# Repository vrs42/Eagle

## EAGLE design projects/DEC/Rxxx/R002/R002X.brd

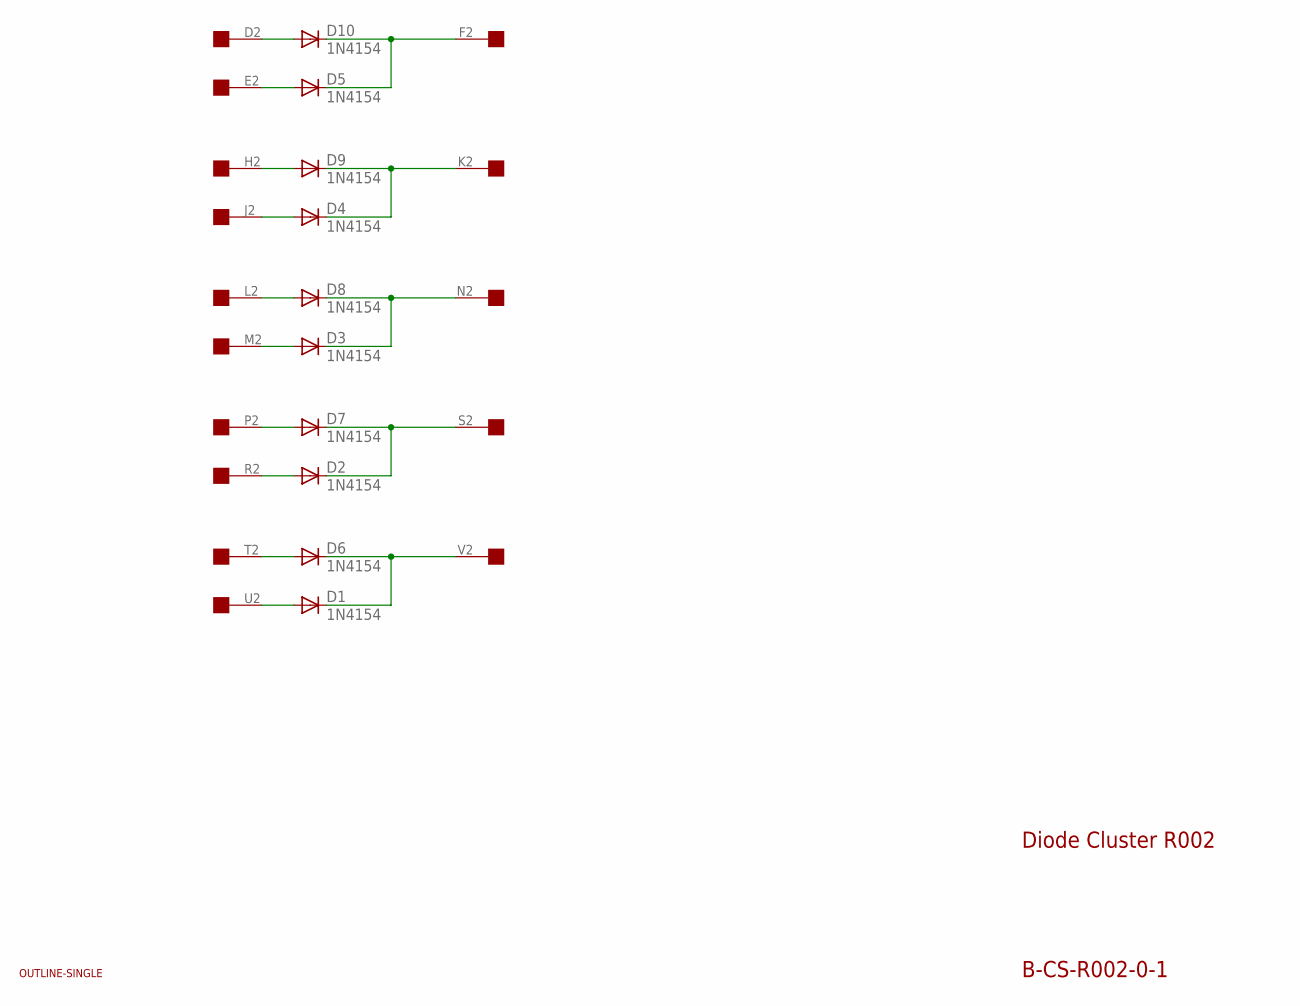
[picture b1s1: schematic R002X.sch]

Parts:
D1, D2, D3, D4, D5, D6, D7, D8, D9, D10: 1N4154; DO35-10
U$1: OUTLINE-SINGLE; SINGLE
U$2: EDGE-1; EDGE-CON1

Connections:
unnamed: D10.A, U$2.D2
unnamed: D5.A, U$2.E2
unnamed: D5.C, D10.C, U$2.F2
unnamed: D9.A, U$2.H2
unnamed: D4.A, U$2.J2
unnamed: D4.C, D9.C, U$2.K2
unnamed: D8.A, U$2.L2
unnamed: D3.A, U$2.M2
unnamed: D3.C, D8.C, U$2.N2
unnamed: D7.A, U$2.P2
unnamed: D2.A, U$2.R2
unnamed: D2.C, D7.C, U$2.S2
unnamed: D6.A, U$2.T2
unnamed: D1.A, U$2.U2
unnamed: D1.C, D6.C, U$2.V2

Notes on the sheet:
Diode Cluster R002
B-CS-R002-0-1

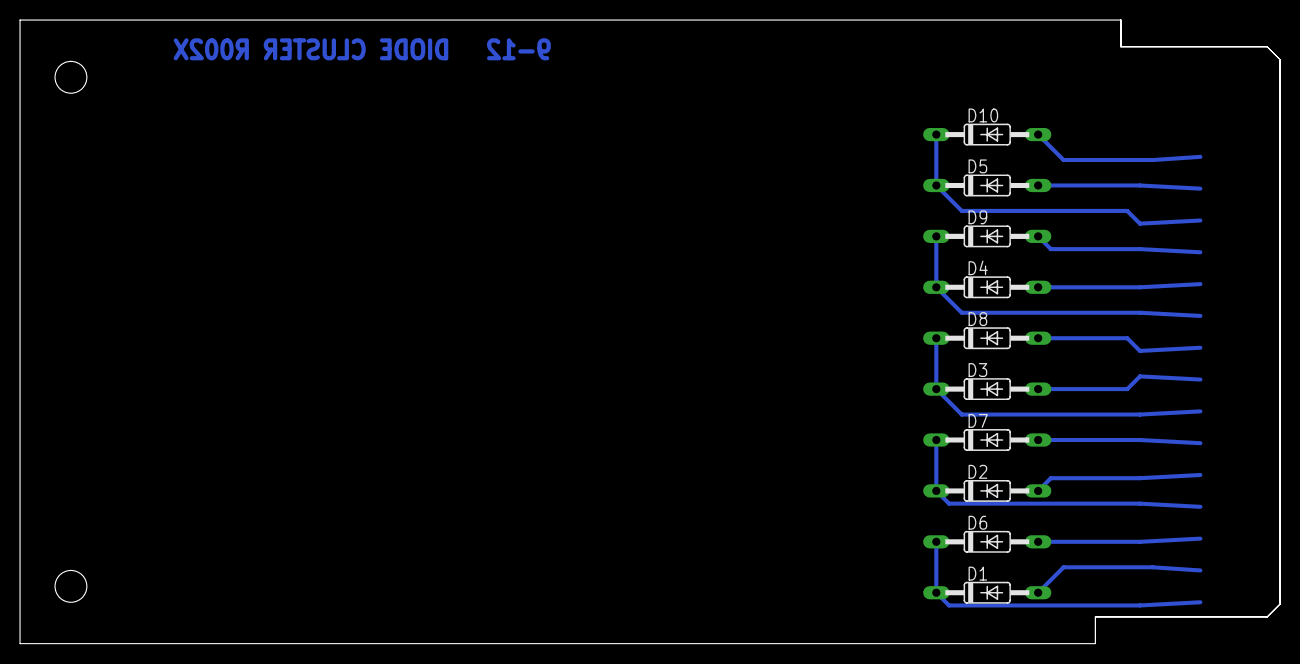
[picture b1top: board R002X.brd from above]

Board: 2 copper layers, 125.7 x 62.2 mm, 12 parts (0 on the bottom side), 15 nets.

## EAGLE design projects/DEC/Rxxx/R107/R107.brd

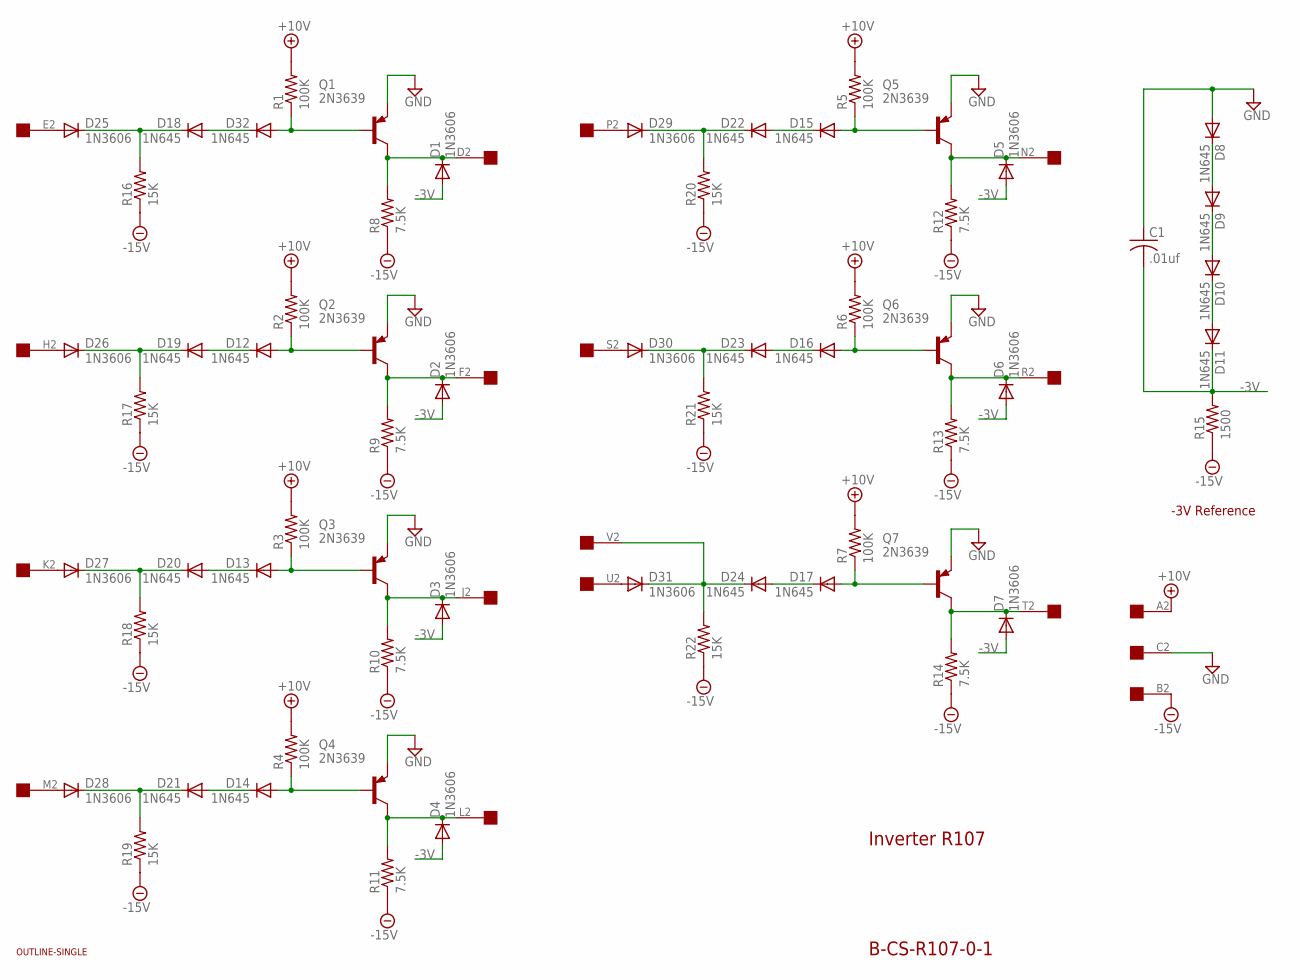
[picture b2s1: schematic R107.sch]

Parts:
C1: .01uf; C050-025X075
D1, D2, D3, D4, D5, D6, D7, D25, D26, D27, D28, D29, D30, D31: 1N3606; DO35-10
D8, D9, D10, D11, D12, D13, D14, D15, D16, D17, D18, D19, D20, D21, D22, D23, D24, D32: 1N645; DO35-10
Q1, Q2, Q3, Q4, Q5, Q6, Q7: 2N3639; TO39
R1, R2, R3, R4, R5, R6, R7: 100K; 0207/10
R8, R9, R10, R11, R12, R13, R14: 7.5K; 0207/10
R15: 1500; 0207/10
R16, R17, R18, R19, R20, R21, R22: 15K; 0207/10
U$1: OUTLINE-SINGLE; SINGLE
U$2: EDGE-1; EDGE-CON1

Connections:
+10V: R1.2, R2.2, R3.2, R4.2, R5.2, R6.2, R7.2, U$2.A2
-3V: C1.2, D1.A, D2.A, D3.A, D4.A, D5.A, D6.A, D7.A, D11.C, R15.2
-15V: R8.1, R9.1, R10.1, R11.1, R12.1, R13.1, R14.1, R15.1, R16.1, R17.1, R18.1, R19.1, R20.1, R21.1, R22.1, U$2.B2
GND: C1.1, D8.A, Q1.1 (E), Q2.1 (E), Q3.1 (E), Q4.1 (E), Q5.1 (E), Q6.1 (E), Q7.1 (E), U$2.C2
unnamed: D7.C, Q7.3 (C), R14.2, U$2.T2
unnamed: D12.A, Q2.2 (B), R2.1
unnamed: D8.C, D9.A
unnamed: D2.C, Q2.3 (C), R9.2, U$2.F2
unnamed: D26.A, U$2.H2
unnamed: D19.C, D26.C, R17.2
unnamed: D12.C, D19.A
unnamed: D13.A, Q3.2 (B), R3.1
unnamed: D3.C, Q3.3 (C), R10.2, U$2.J2
unnamed: D27.A, U$2.K2
unnamed: D20.C, D27.C, R18.2
unnamed: D13.C, D20.A
unnamed: D9.C, D10.A
unnamed: D31.A, U$2.U2
unnamed: D17.A, Q7.2 (B), R7.1
unnamed: D10.C, D11.A
unnamed: D24.C, D31.C, R22.2, U$2.V2
unnamed: D17.C, D24.A
unnamed: D32.A, Q1.2 (B), R1.1
unnamed: D1.C, Q1.3 (C), R8.2, U$2.D2
unnamed: D25.A, U$2.E2
unnamed: D18.C, D25.C, R16.2
unnamed: D18.A, D32.C
unnamed: D14.A, Q4.2 (B), R4.1
unnamed: D4.C, Q4.3 (C), R11.2, U$2.L2
unnamed: D28.A, U$2.M2
unnamed: D21.C, D28.C, R19.2
unnamed: D14.C, D21.A
unnamed: D15.A, Q5.2 (B), R5.1
unnamed: D5.C, Q5.3 (C), R12.2, U$2.N2
unnamed: D29.A, U$2.P2
unnamed: D22.C, D29.C, R20.2
unnamed: D15.C, D22.A
unnamed: D16.A, Q6.2 (B), R6.1
unnamed: D6.C, Q6.3 (C), R13.2, U$2.R2
unnamed: D30.A, U$2.S2
unnamed: D23.C, D30.C, R21.2
unnamed: D16.C, D23.A

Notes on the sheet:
Inverter R107
B-CS-R107-0-1
-3V Reference

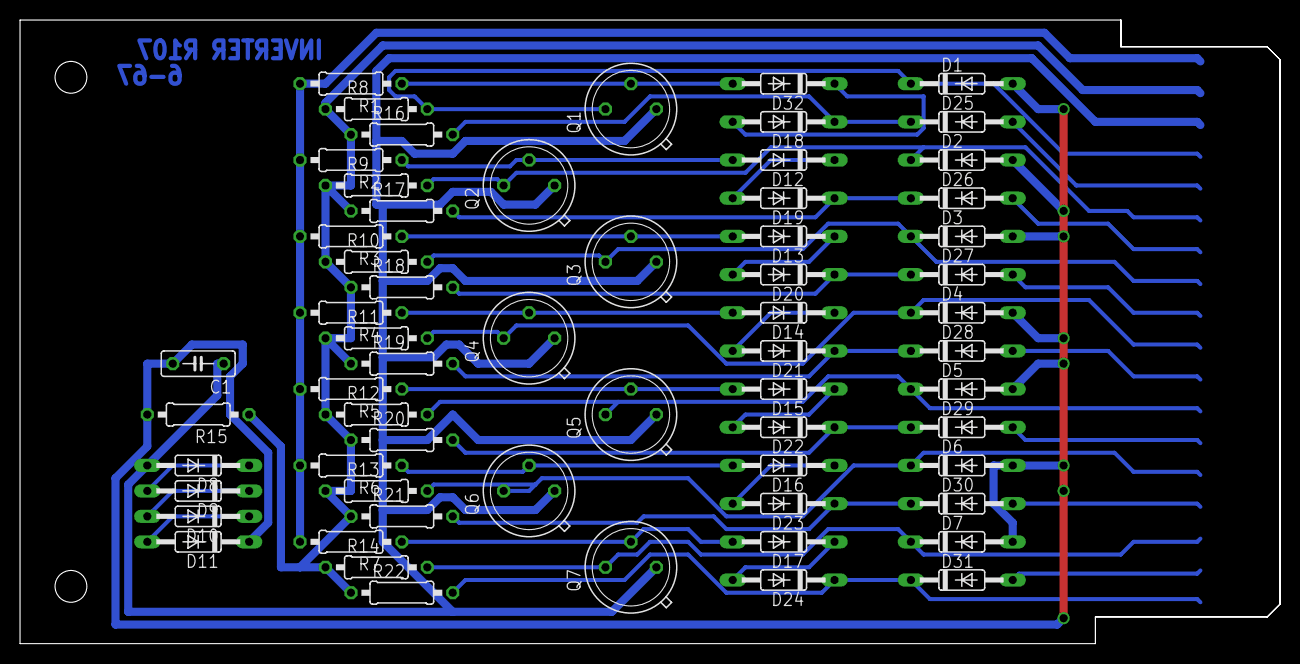
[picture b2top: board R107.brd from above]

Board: 2 copper layers, 125.7 x 62.2 mm, 64 parts (0 on the bottom side), 42 nets.

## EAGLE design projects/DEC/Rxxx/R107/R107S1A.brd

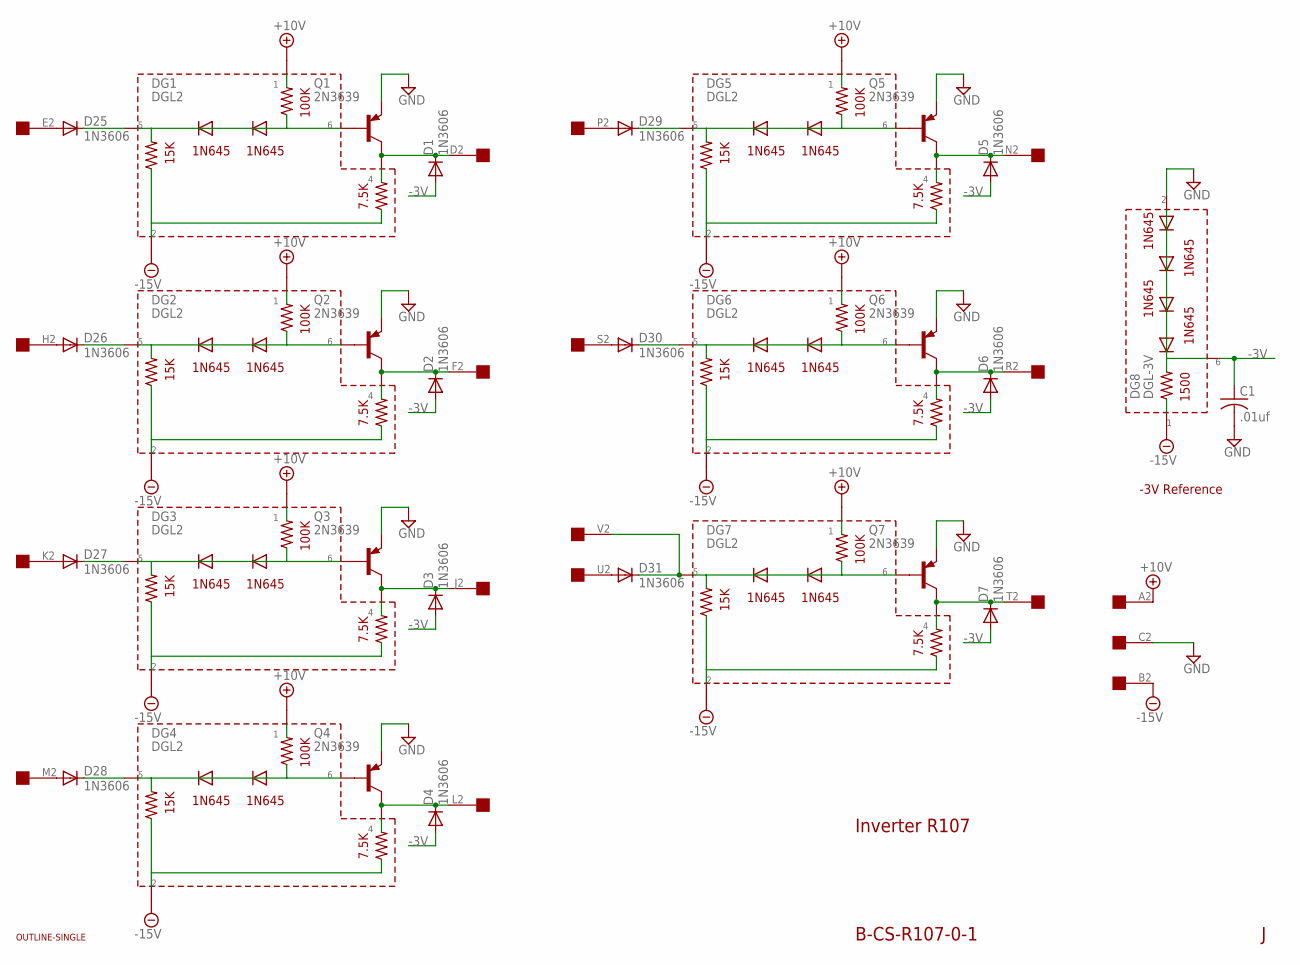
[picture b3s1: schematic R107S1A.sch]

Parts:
C1: .01uf; C050-025X075
D1, D2, D3, D4, D5, D6, D7, D25, D26, D27, D28, D29, D30, D31: 1N3606; DO35-10
DG1, DG2, DG3, DG4, DG5, DG6, DG7: DGL2
DG8: DGL-3V; DGL2
Q1, Q2, Q3, Q4, Q5, Q6, Q7: 2N3639; TO39
U$1: OUTLINE-SINGLE; SINGLE
U$2: EDGE-1; EDGE-CON1

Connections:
+10V: DG1.P$1 (1), DG2.P$1 (1), DG3.P$1 (1), DG4.P$1 (1), DG5.P$1 (1), DG6.P$1 (1), DG7.P$1 (1), U$2.A2
-3V: C1.1, D1.A, D2.A, D3.A, D4.A, D5.A, D6.A, D7.A, DG8.P$6 (6)
-15V: DG1.P$2 (2), DG2.P$2 (2), DG3.P$2 (2), DG4.P$2 (2), DG5.P$2 (2), DG6.P$2 (2), DG7.P$2 (2), DG8.P$1 (1), U$2.B2
GND: C1.2, DG8.P$2 (2), Q1.1 (E), Q2.1 (E), Q3.1 (E), Q4.1 (E), Q5.1 (E), Q6.1 (E), Q7.1 (E), U$2.C2
unnamed: D7.C, DG7.P$4 (4), Q7.3 (C), U$2.T2
unnamed: DG2.P$6 (6), Q2.2 (B)
unnamed: D2.C, DG2.P$4 (4), Q2.3 (C), U$2.F2
unnamed: D26.A, U$2.H2
unnamed: DG3.P$6 (6), Q3.2 (B)
unnamed: DG4.P$6 (6), Q4.2 (B)
unnamed: D26.C, DG2.P$5 (5)
unnamed: D3.C, DG3.P$4 (4), Q3.3 (C), U$2.J2
unnamed: D27.A, U$2.K2
unnamed: D27.C, DG3.P$5 (5)
unnamed: D28.C, DG4.P$5 (5)
unnamed: D31.A, U$2.U2
unnamed: DG5.P$6 (6), Q5.2 (B)
unnamed: D31.C, DG7.P$5 (5), U$2.V2
unnamed: DG6.P$6 (6), Q6.2 (B)
unnamed: DG1.P$6 (6), Q1.2 (B)
unnamed: D1.C, DG1.P$4 (4), Q1.3 (C), U$2.D2
unnamed: D25.A, U$2.E2
unnamed: D25.C, DG1.P$5 (5)
unnamed: DG7.P$6 (6), Q7.2 (B)
unnamed: D30.C, DG6.P$5 (5)
unnamed: D4.C, DG4.P$4 (4), Q4.3 (C), U$2.L2
unnamed: D28.A, U$2.M2
unnamed: D5.C, DG5.P$4 (4), Q5.3 (C), U$2.N2
unnamed: D29.A, U$2.P2
unnamed: D29.C, DG5.P$5 (5)
unnamed: D6.C, DG6.P$4 (4), Q6.3 (C), U$2.R2
unnamed: D30.A, U$2.S2

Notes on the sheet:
Inverter R107
B-CS-R107-0-1
-3V Reference

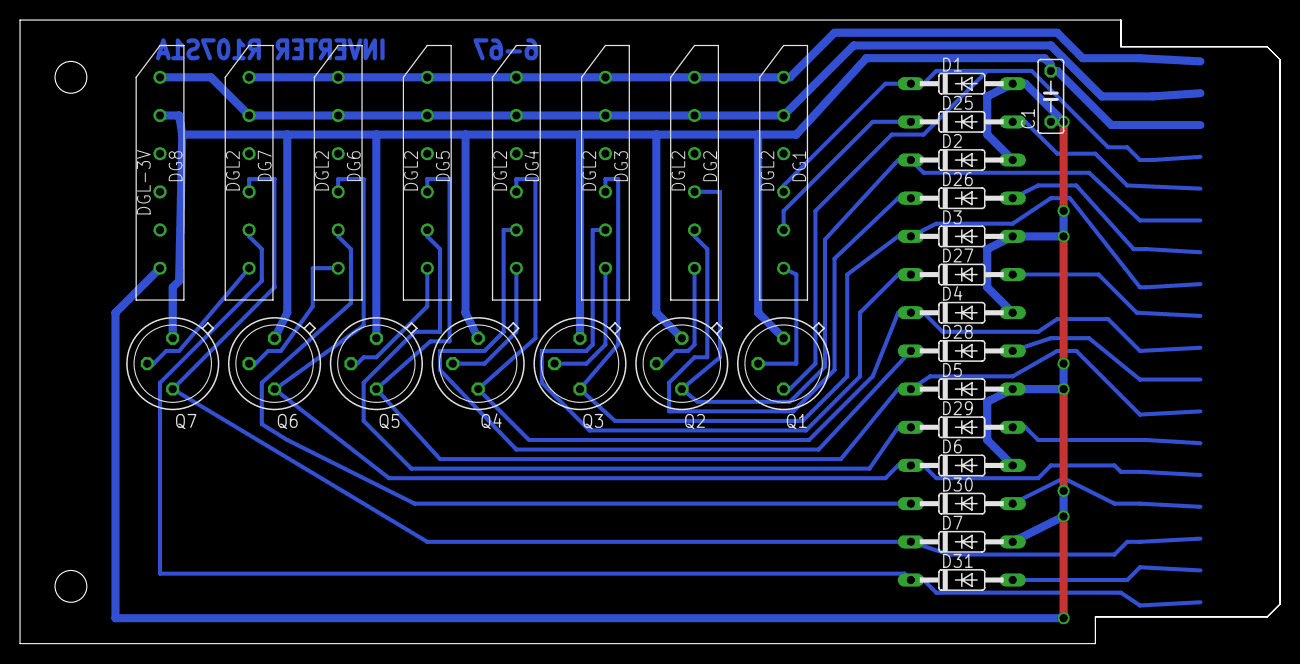
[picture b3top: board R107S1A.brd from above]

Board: 2 copper layers, 125.7 x 62.2 mm, 32 parts (0 on the bottom side), 32 nets.
